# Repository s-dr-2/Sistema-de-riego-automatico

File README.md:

# Sistema-de-riego-automatico
En este repositorio se va a mostrar la evolucion y algunos aspectos importantes del proyecto que se va  a realizar de la mano con el docente encargado de la asignatura de taller de ingenieria electronica

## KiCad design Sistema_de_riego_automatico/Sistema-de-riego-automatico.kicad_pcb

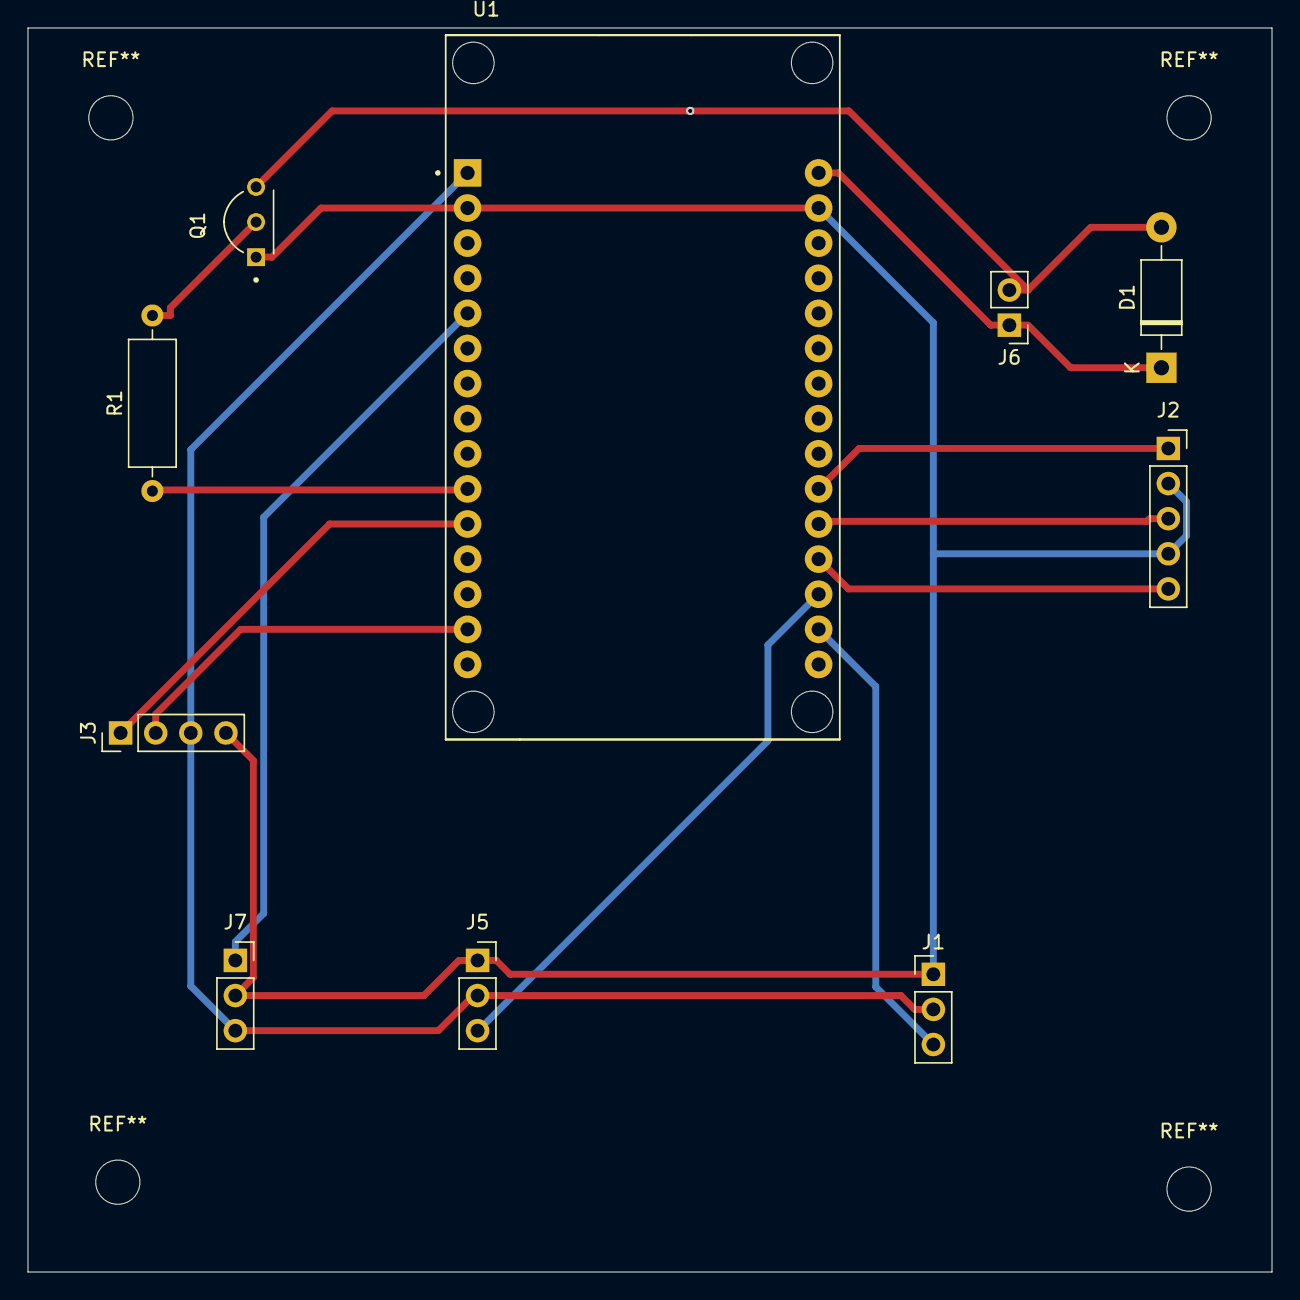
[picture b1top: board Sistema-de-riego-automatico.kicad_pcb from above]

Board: 2 copper layers, 90.0 x 90.0 mm, 10 parts (0 on the bottom side), 14 nets.

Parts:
D1: 1N4004; D_DO-41_SOD81_P10.16mm_Horizontal
J1: Sensor nivel de agua; PinHeader_1x03_P2.54mm_Vertical
J2: Encoder rotativo; PinSocket_1x05_P2.54mm_Vertical
J3: Pantalla OLED; PinHeader_1x04_P2.54mm_Vertical
J5: Sensor humedad; PinSocket_1x03_P2.54mm_Vertical
J6: Bomba de agua; PinHeader_1x02_P2.54mm_Vertical
J7: Sensor de temperatura; PinSocket_1x03_P2.54mm_Vertical
Q1: 2N2222A; TO92254P470H750-3
R1: R; R_Axial_DIN0309_L9.0mm_D3.2mm_P12.70mm_Horizontal
U1: ESP32-DEVKIT-V1; MODULE_ESP32_DEVKIT_V1

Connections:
+3.3V: J1.2, J3.3, J5.2, J7.3, U1.1 (3V3)
/Output_A: J2.3, U1.20 (D35)
/Output_B: J2.5, U1.19 (D34)
/PWM_B: R1.1, U1.10 (D19)
/P_B: D1.1 (K), J6.1, U1.30 (VIN)
/SCL: J3.2, U1.14 (D22)
/SDA: J3.1, U1.11 (D21)
/S_HM: J5.3, U1.18 (VN)
/S_SN: J1.3, U1.17 (VP)
/S_T: J7.1, U1.5 (D4)
/Switch: J2.1, U1.21 (D32)
GND: J1.1, J2.2, J2.4, J3.4, J5.1, J7.2, Q1.1, U1.2 (GND), U1.29 (GND)
unnamed: D1.2 (A), J6.2, Q1.3
unnamed: Q1.2, R1.2

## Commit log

2025-02-04 Diagrama de flujo.drawio
2025-02-04 Actualizar Diagrama sin título.drawio
2025-02-08 Agregado Diagrama de caja negra.drawio
2025-02-08 Actualizar Diagrama de caja negra.drawio
2025-03-05 Diagrama tecnologico
2025-03-07 Agregado Diagrama de flujo tareas proyecto.drawio
2025-03-07 Actualizar Diagrama de flujo tareas proyecto.drawio
2025-03-08 Diseño del circuito electrónico y PCB en KiCad
2025-03-08 Create Código fuente mycropython para ESP32
    Código fuente del proyecto, escrito en micropython para ser ejecutado en ESP32.
    Software usado: Thonny
    nombre del archivo: main.py
2025-03-08 main.py
    Código fuente del programa de control de la ESP32
2025-03-08 2N2222A
2025-03-08 Create read
